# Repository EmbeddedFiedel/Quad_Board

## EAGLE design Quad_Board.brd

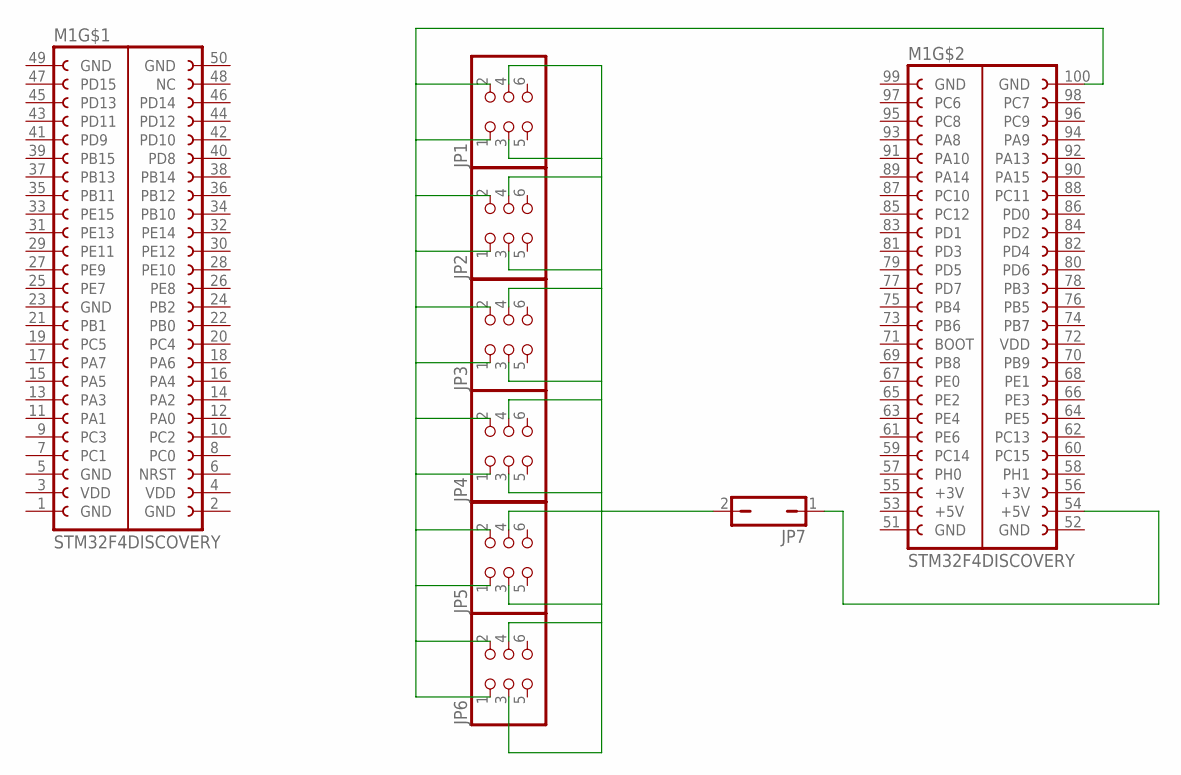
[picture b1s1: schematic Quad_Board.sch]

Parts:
JP1, JP2, JP3, JP4, JP5, JP6: PINHD-2X3; 2X03
JP7: JP1Q; JP1
M1: STM32F4DISCOVERY

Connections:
unnamed: JP1.1, JP1.2, JP2.1, JP2.2, JP3.1, JP3.2, JP4.1, JP4.2, JP5.1, JP5.2, JP6.1, JP6.2, M1.100 (GND)
unnamed: JP7.1, M1.54 (+5V)
unnamed: JP1.3, JP1.4, JP2.3, JP2.4, JP3.3, JP3.4, JP4.3, JP4.4, JP5.3, JP5.4, JP6.3, JP6.4, JP7.2

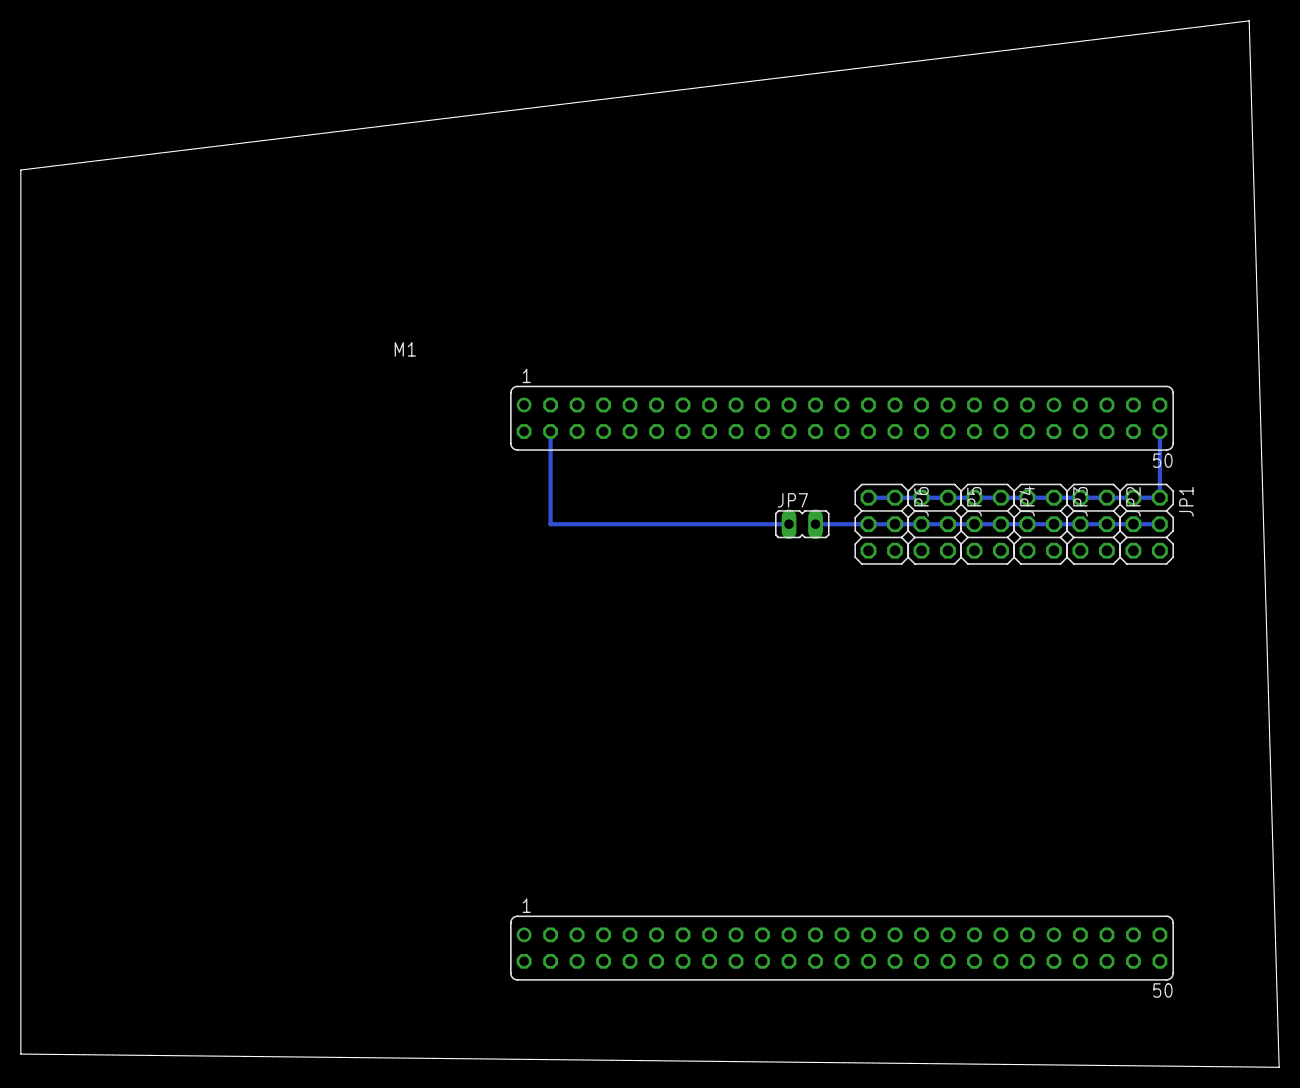
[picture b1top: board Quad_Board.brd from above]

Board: 2 copper layers, 120.6 x 100.3 mm, 8 parts (0 on the bottom side), 3 nets.

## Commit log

2013-01-16 Schnittstellenliste
